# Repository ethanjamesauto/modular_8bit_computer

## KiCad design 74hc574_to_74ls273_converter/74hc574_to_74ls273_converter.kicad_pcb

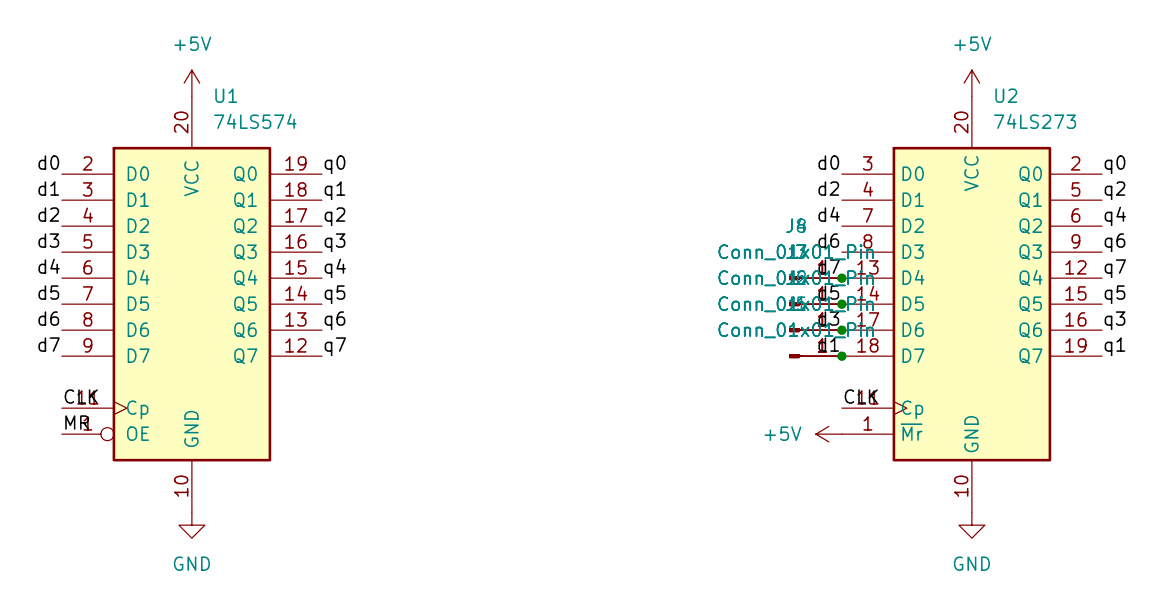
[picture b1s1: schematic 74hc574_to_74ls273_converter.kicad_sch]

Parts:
J1, J2, J3, J4, J5, J6, J7, J8: Conn_01x01_Pin; PinHeader_1x01_P2.54mm_Vertical
U1: 74LS574; DIP-20_W7.62mm
U2: 74LS273; DIP-20_W7.62mm

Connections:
+5V: U1.20 (VCC), U2.1 (~Mr), U2.20 (VCC)
/CLK: U1.11 (Cp), U2.11 (Cp)
/MR: U1.1 (OE)
/d0: U1.2 (D0), U2.3 (D0)
/d1: J1.1, J5.1, U1.3 (D1), U2.18 (D7)
/d2: U1.4 (D2), U2.4 (D1)
/d3: J2.1, J6.1, U1.5 (D3), U2.17 (D6)
/d4: U1.6 (D4), U2.7 (D2)
/d5: J3.1, J7.1, U1.7 (D5), U2.14 (D5)
/d6: U1.8 (D6), U2.8 (D3)
/d7: J4.1, J8.1, U1.9 (D7), U2.13 (D4)
/q0: U1.19 (Q0), U2.2 (Q0)
/q1: U1.18 (Q1), U2.19 (Q7)
/q2: U1.17 (Q2), U2.5 (Q1)
/q3: U1.16 (Q3), U2.16 (Q6)
/q4: U1.15 (Q4), U2.6 (Q2)
/q5: U1.14 (Q5), U2.15 (Q5)
/q6: U1.13 (Q6), U2.9 (Q3)
/q7: U1.12 (Q7), U2.12 (Q4)
GND: U1.10 (GND), U2.10 (GND)

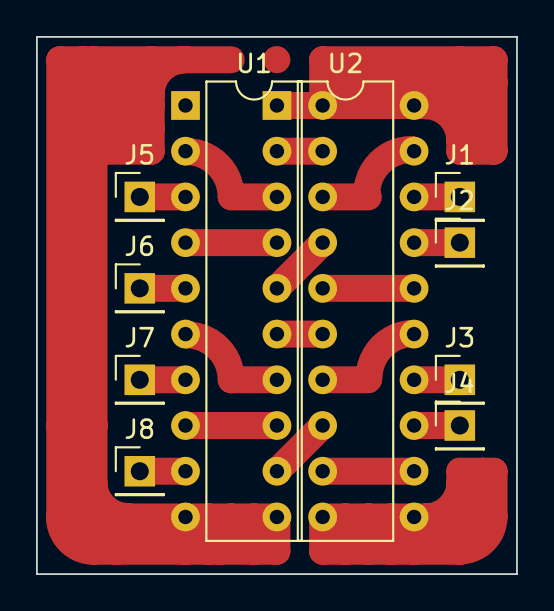
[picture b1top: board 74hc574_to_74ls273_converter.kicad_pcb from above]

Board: 2 copper layers, 26.7 x 29.8 mm, 10 parts (0 on the bottom side), 19 nets.

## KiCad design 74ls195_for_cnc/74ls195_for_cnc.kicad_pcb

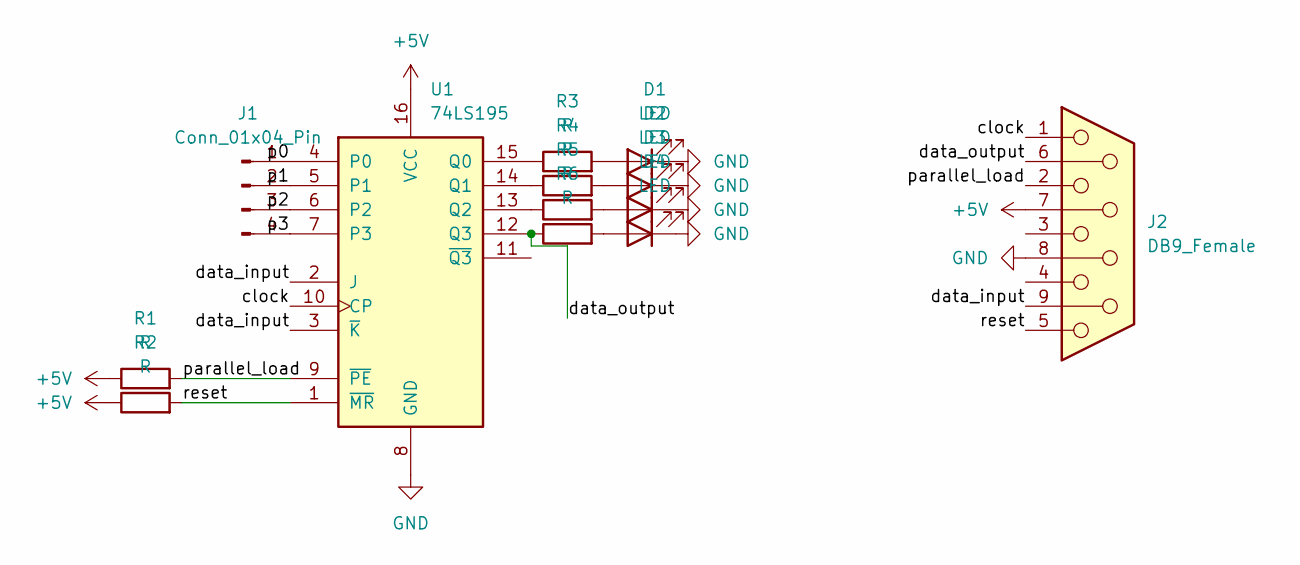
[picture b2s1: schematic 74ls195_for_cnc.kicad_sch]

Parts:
D1, D2, D3, D4: LED; LED_D5.0mm
J1: Conn_01x04_Pin; PinHeader_1x04_P2.54mm_Vertical
J2: DB9_Female; DSUB-9_Female_Horizontal_P2.77x2.54mm_EdgePinOffset9.40mm
R1, R2, R3, R4, R5, R6: R; R_Axial_DIN0204_L3.6mm_D1.6mm_P7.62mm_Horizontal
U1: 74LS195; DIP-16_W7.62mm

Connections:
+5V: J2.7, R1.1, R2.1, U1.16 (VCC)
/clock: J2.1, U1.10 (CP)
/data_input: J2.9, U1.2 (J), U1.3 (~K)
/data_output: J2.6, R6.1, U1.12 (Q3)
/p0: J1.1, U1.4 (P0)
/p1: J1.2, U1.5 (P1)
/p2: J1.3, U1.6 (P2)
/p3: J1.4, U1.7 (P3)
/parallel_load: J2.2, R1.2, U1.9 (~PE)
/reset: J2.5, R2.2, U1.1 (~MR)
GND: D1.1 (K), D2.1 (K), D3.1 (K), D4.1 (K), J2.8, U1.8 (GND)
unnamed: D1.2 (A), R3.2
unnamed: D2.2 (A), R4.2
unnamed: D3.2 (A), R5.2
unnamed: D4.2 (A), R6.2
unnamed: R3.1, U1.15 (Q0)
unnamed: R4.1, U1.14 (Q1)
unnamed: R5.1, U1.13 (Q2)

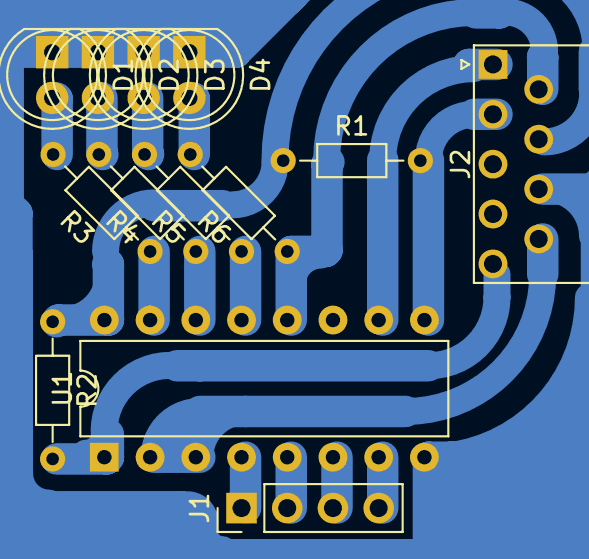
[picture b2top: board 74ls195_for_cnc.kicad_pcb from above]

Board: 2 copper layers, 13 parts (0 on the bottom side), 18 nets.

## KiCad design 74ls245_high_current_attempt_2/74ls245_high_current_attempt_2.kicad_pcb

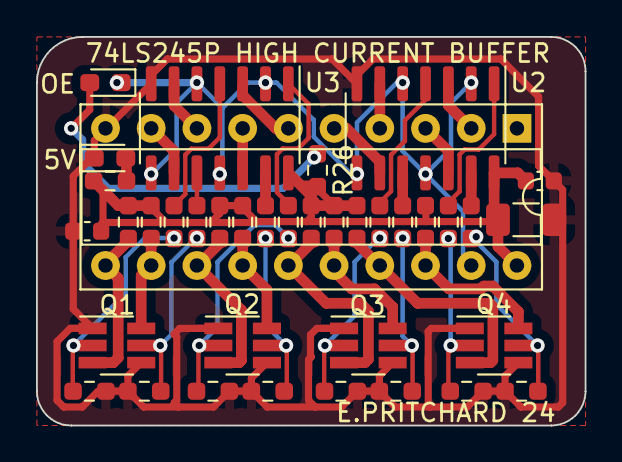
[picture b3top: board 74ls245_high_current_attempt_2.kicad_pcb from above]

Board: 2 copper layers, 30.5 x 21.6 mm, 38 parts (0 on the bottom side), 37 nets.

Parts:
5V: LED; LED_0603_1608Metric_Pad1.05x0.95mm_HandSolder
C1: C; C_1206_3216Metric_Pad1.33x1.80mm_HandSolder
C2, C4: 1uF; C_0603_1608Metric
OE: OE; LED_0603_1608Metric_Pad1.05x0.95mm_HandSolder
Q1, Q2, Q3, Q4: FDG1024NZ; SOT-23-6_Handsoldering
R1, R2, R7, R10, R13, R16, R19, R22: 4.7; R_0603_1608Metric_Pad0.98x0.95mm_HandSolder
R3, R4, R5, R6, R8, R9, R11, R12, R14, R15, R17, R18, R20, R21, R23, R24: 10k; R_0603_1608Metric_Pad0.98x0.95mm_HandSolder
R25, R26: 470; R_0603_1608Metric_Pad0.98x0.95mm_HandSolder
U1: 74LS245_USED_FOR_FOOTPRINT; DIP-20_W7.62mm_Socket
U2, U3: 74LS02; SOIC-14_3.9x8.7mm_P1.27mm

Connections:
+5V: C1.1, C2.1, C4.1, R3.2, R6.2, R9.2, R12.2, R15.2, R18.2, R21.2, R24.2, R25.2, R26.2, U1.20 (VCC), U2.14 (VCC), U3.14 (VCC)
/BUFFER_OE: OE.1 (K), U1.19 (CE), U2.2, U2.5, U2.8, U2.11, U3.2, U3.5, U3.8, U3.11
/in_0: U1.2 (A0), U2.3
/in_1: U1.3 (A1), U2.12
/in_2: U1.4 (A2), U2.6
/in_3: U1.5 (A3), U2.9
/in_4: U1.6 (A4), U3.3
/in_5: U1.7 (A5), U3.12
/in_6: U1.8 (A6), U3.6
/in_7: U1.9 (A7), U3.9
/out_0: Q4.6 (D), R3.1, U1.18 (B0)
/out_1: Q4.3 (D), R6.1, U1.17 (B1)
/out_2: Q3.6 (D), R21.1, U1.16 (B2)
/out_3: Q3.3 (D), R24.1, U1.15 (B3)
/out_4: Q2.6 (D), R15.1, U1.14 (B4)
/out_5: Q2.3 (D), R18.1, U1.13 (B5)
/out_6: Q1.6 (D), R9.1, U1.12 (B6)
/out_7: Q1.3 (D), R12.1, U1.11 (B7)
GND: 5V.1 (K), C1.2, C2.2, C4.2, Q1.1 (S), Q1.4 (S), Q2.1 (S), Q2.4 (S), Q3.1 (S), Q3.4 (S), Q4.1 (S), Q4.4 (S), R4.1, R5.1, R8.1, R11.1, R14.1, R17.1, R20.1, R23.1, U1.10 (GND), U2.7 (GND), U3.7 (GND)
unnamed: 5V.2 (A), R25.1
unnamed: OE.2 (A), R26.1
unnamed: Q1.2 (G), R7.2, R8.2
unnamed: Q1.5 (G), R10.2, R11.2
unnamed: Q2.2 (G), R13.2, R14.2
unnamed: Q2.5 (G), R16.2, R17.2
unnamed: Q3.2 (G), R19.2, R20.2
unnamed: Q3.5 (G), R22.2, R23.2
unnamed: Q4.2 (G), R2.2, R4.2
unnamed: Q4.5 (G), R1.2, R5.2
unnamed: R1.1, U2.13
unnamed: R2.1, U2.1
unnamed: R7.1, U3.4
unnamed: R10.1, U3.10
unnamed: R13.1, U3.1
unnamed: R16.1, U3.13
unnamed: R19.1, U2.4
unnamed: R22.1, U2.10

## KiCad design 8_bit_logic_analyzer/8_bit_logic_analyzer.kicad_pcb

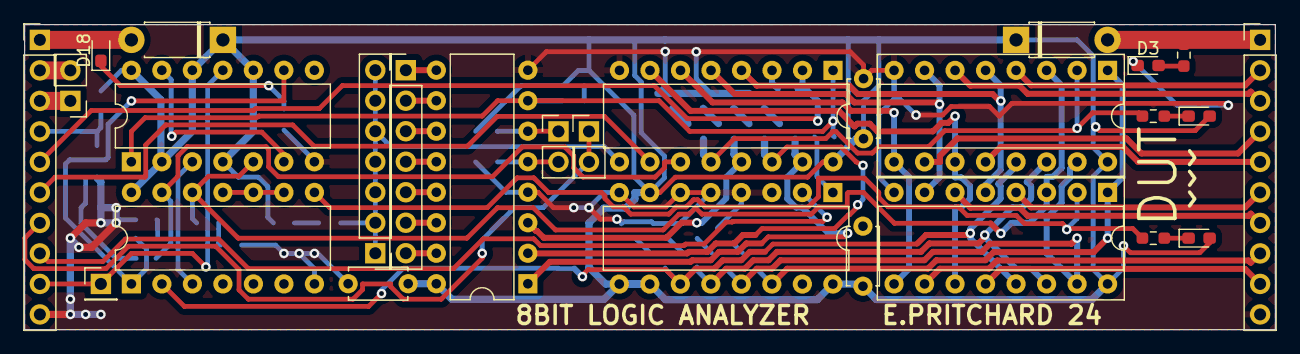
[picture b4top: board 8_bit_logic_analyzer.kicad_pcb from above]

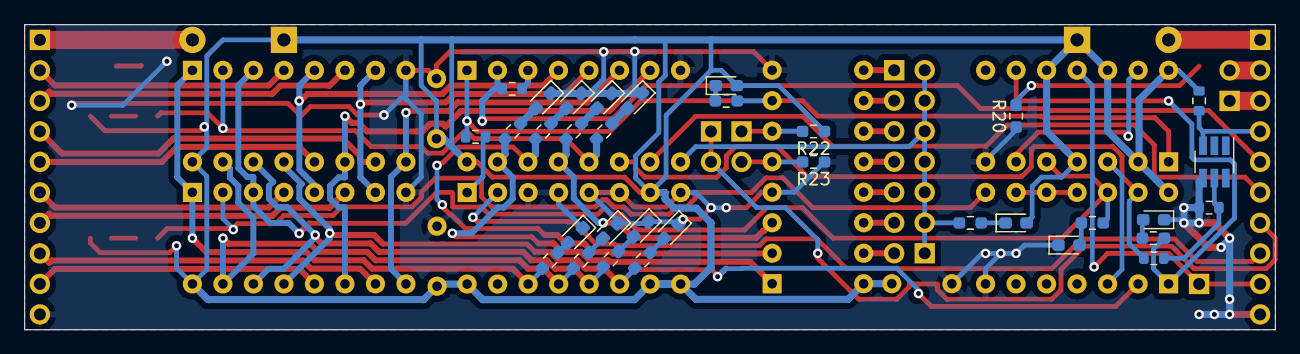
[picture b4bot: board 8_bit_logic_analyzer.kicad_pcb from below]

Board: 2 copper layers, 104.1 x 25.4 mm, 60 parts (33 on the bottom side), 69 nets.

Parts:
C4: 100nF; C_Disc_D4.7mm_W2.5mm_P5.00mm
C10, C11: 1uF; C_Disc_D4.7mm_W2.5mm_P5.00mm
D1, D2: D; D_DO-41_SOD81_P7.62mm_Horizontal
D3, D4, D5, D6, D7, D8, D9, D10, D11, D12, D13, D14, D15, D16, D17, D18: LED; LED_0603_1608Metric_Pad1.05x0.95mm_HandSolder
J1, J2: Conn_01x10_Pin; PinHeader_1x10_P2.54mm_Vertical
J3, J4: Conn_01x07_Pin; PinHeader_1x07_P2.54mm_Vertical
J5, J6, J7: Conn_01x02_Pin; PinHeader_1x02_P2.54mm_Vertical
J8: Conn_01x01_Pin; PinHeader_1x01_P2.54mm_Vertical
Q1: FDG1024NZ; SOT-23-6_Handsoldering
R1: 4.7; R_0603_1608Metric
R2, R3: 10k; R_0603_1608Metric
R4, R6, R7, R8, R9, R10, R11, R12, R13, R14, R15, R16, R17, R18, R19, R20, R22, R23: 470; R_0603_1608Metric_Pad0.98x0.95mm_HandSolder
R5, R21: 0; R_0603_1608Metric
U2, U4: DIP-16_W7.62mm_Socket
U5: 74LS195; DIP-16_W7.62mm
U6: 74LS138; DIP-16_W7.62mm
U7: 74LS74; DIP-14_W7.62mm
U8: 74LS00; DIP-14_W7.62mm
U9: 74LS161; DIP-16_W7.62mm

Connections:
/A: J1.2, U2.4 (D0)
/B: J1.3, U2.6 (D1)
/C: J1.4, U2.10 (D2)
/D: J1.5, U2.12 (D3)
/E: J1.6, U4.4 (D0)
/F: J1.7, U4.6 (D1)
/G: J1.8, U4.10 (D2)
/H: J1.9, U4.12 (D3)
/card_selected: J4.1, J4.2, J4.3, J4.4, J4.5, J4.6, J4.7, R6.2, U5.9 (~PE)
/clear_command: R7.2, R21.2, U5.1 (~MR), U6.7 (O7), U7.1 (~R)
/logic_analyzer_addr_0: R14.2, U2.1 (A0), U4.1 (A0), U9.14 (Q0)
/logic_analyzer_addr_1: R15.2, U2.15 (A1), U4.15 (A1), U9.13 (Q1)
/logic_analyzer_addr_2: R16.2, U2.14 (A2), U4.14 (A2), U9.12 (Q2)
/logic_analyzer_addr_3: R17.2, U2.13 (A3), U4.13 (A3), U8.2, U9.11 (Q3)
/logic_analyzer_data_0: U2.5 (S0_n), U4.5 (S0_n), U5.4 (P0)
/logic_analyzer_data_1: U2.7 (S1_n), U4.7 (S1_n), U5.5 (P1)
/logic_analyzer_data_2: U2.9 (S2_n), U4.9 (S2_n), U5.6 (P2)
/logic_analyzer_data_3: U2.11 (S3_n), U4.11 (S3_n), U5.7 (P3)
/rec_clock: J2.8, U9.2 (CP)
/rec_trig: J2.9, J8.1, U7.11 (C)
/s_clock: J2.6, U5.10 (CP)
/s_cs: J2.7, J6.1, J6.2
/s_data_in: J2.5, R5.1, U5.2 (J)
/s_data_out: J2.4, Q1.3 (D), R3.1
/~ram_0_selected: R11.2, R18.2, U2.2 (~CS), U5.12 (Q3)
/~ram_1_selected: R1.1, U5.11 (~Q3), U8.13
/~record: R13.2, U2.3 (~WE), U4.3 (~WE), U7.5 (Q), U8.12
/~record_halt: U7.6 (~Q), U7.13 (~R)
GND: C4.2, C10.2, C11.2, D3.1 (K), D6.1 (K), D7.1 (K), D8.1 (K), D9.1 (K), D10.1 (K), D11.1 (K), D12.1 (K), D13.1 (K), D14.1 (K), D15.1 (K), J1.10, J2.10, Q1.4 (S), R2.1, R20.1, R23.1, U2.8 (GND), U4.8 (GND), U5.8 (GND), U6.4 (E1), U6.8 (GND), U7.7 (GND), U8.7 (GND), U9.3 (D0), U9.4 (D1), U9.5 (D2), U9.6 (D3), U9.8 (GND)
unnamed: D1.2 (A), D18.2 (A), J2.1
unnamed: D2.2 (A), J1.1, R4.2
unnamed: D3.2 (A), R4.1
unnamed: D4.1 (K), R6.1
unnamed: D5.1 (K), R7.1
unnamed: D6.2 (A), R8.1
unnamed: D7.2 (A), R9.1
unnamed: D8.2 (A), R10.1
unnamed: D9.2 (A), R11.1
unnamed: D10.2 (A), R12.1
unnamed: D11.2 (A), R13.1
unnamed: D12.2 (A), R14.1
unnamed: D13.2 (A), R15.1
unnamed: D14.2 (A), R16.1
unnamed: D15.2 (A), R17.1
unnamed: D16.1 (K), R18.1
unnamed: D17.1 (K), R19.1
unnamed: D18.1 (K), R20.2
unnamed: J2.2, J7.2
unnamed: J2.3, J7.1
unnamed: J3.1, U6.9 (O6)
unnamed: J3.2, U6.10 (O5)
unnamed: J3.3, U6.11 (O4)
unnamed: J3.4, U6.12 (O3)
unnamed: J3.5, U6.13 (O2)
unnamed: J3.6, U6.14 (O1)
unnamed: J3.7, U6.15 (O0)
unnamed: J5.1, R22.2, U6.6 (E3)
unnamed: J5.2, R23.2, U6.5 (E2)
unnamed: Q1.5 (G), R1.2, R2.2
unnamed: R19.2, U4.2 (~CS), U8.8
unnamed: R8.2, U5.15 (Q0), U6.1 (A0)
unnamed: R9.2, U5.14 (Q1), U6.2 (A1)
unnamed: R10.2, U5.13 (Q2), U6.3 (A2)
unnamed: R5.2, U5.3 (~K)
unnamed: U7.3 (C), U8.3
unnamed: R12.2, U7.9 (Q), U8.1
unnamed: U8.9, U8.10, U8.11
unnamed: R21.1, U9.1 (~MR)
VCC: C4.1, C10.1, C11.1, D1.1 (K), D2.1 (K), D4.2 (A), D5.2 (A), D16.2 (A), D17.2 (A), R3.2, R22.1, U2.16 (VCC), U4.16 (VCC), U5.16 (VCC), U6.16 (VCC), U7.2 (D), U7.4 (~S), U7.10 (~S), U7.12 (D), U7.14 (VCC), U8.14 (VCC), U9.7 (CEP), U9.9 (~PE), U9.10 (CET), U9.16 (VCC)

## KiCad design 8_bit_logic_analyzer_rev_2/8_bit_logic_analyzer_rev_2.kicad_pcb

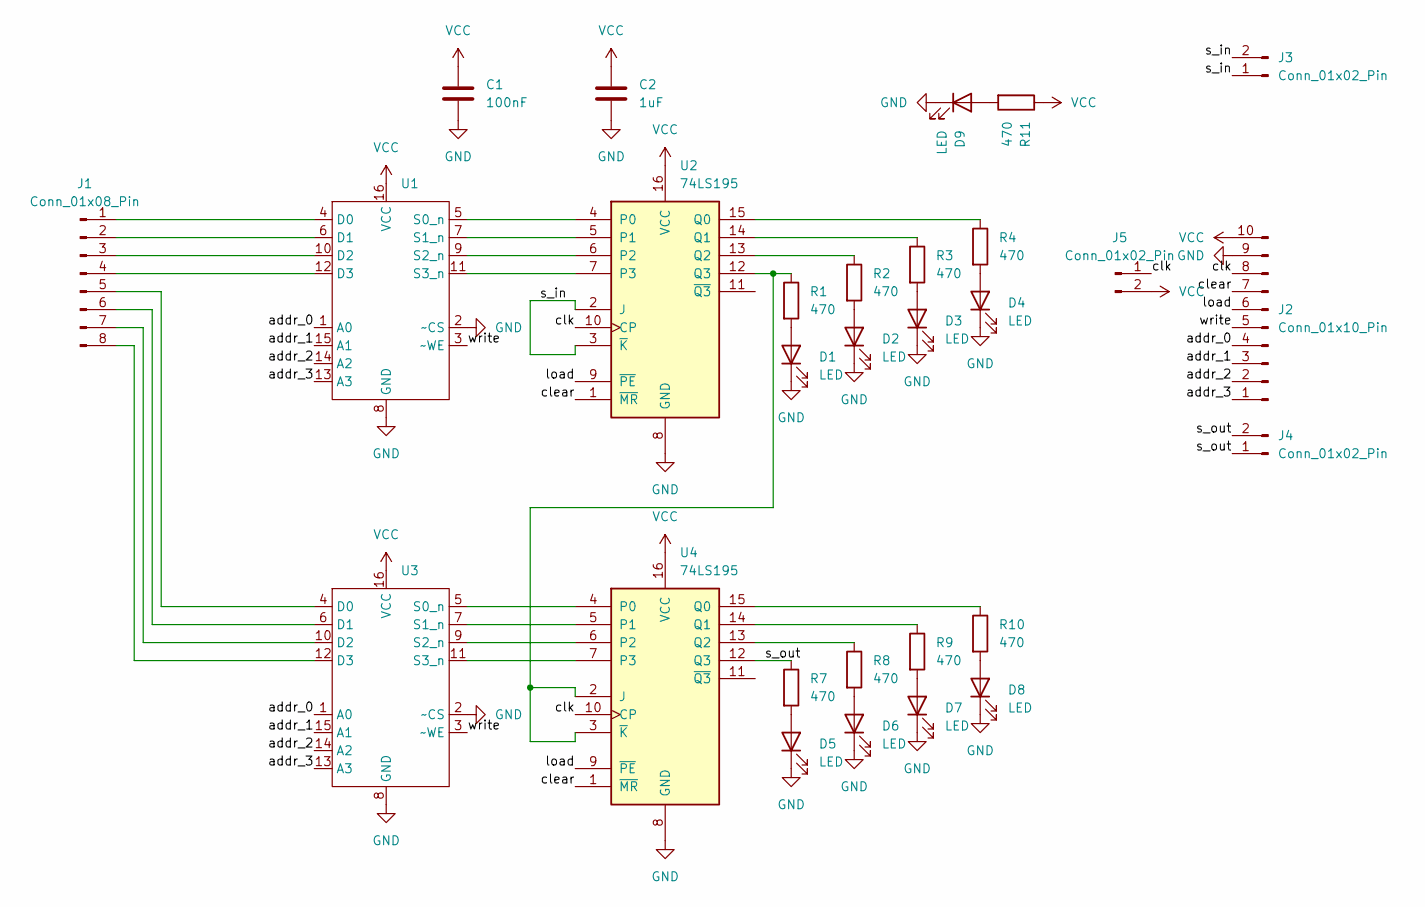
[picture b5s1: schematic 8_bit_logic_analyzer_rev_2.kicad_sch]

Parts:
C1: 100nF; C_Disc_D3.0mm_W2.0mm_P2.50mm
C2: 1uF; C_Disc_D3.0mm_W2.0mm_P2.50mm
D1, D2, D3, D4, D5, D6, D7, D8, D9: LED; R_0603_1608Metric
J1: Conn_01x08_Pin; PinHeader_1x08_P2.54mm_Vertical
J2: Conn_01x10_Pin; PinHeader_1x10_P2.54mm_Vertical
J3, J4, J5: Conn_01x02_Pin; PinHeader_1x02_P2.54mm_Vertical
R1, R2, R3, R4, R7, R8, R9, R10, R11: 470; R_0603_1608Metric
U1, U3: DIP-16_W7.62mm
U2, U4: 74LS195; DIP-16_W7.62mm

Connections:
/addr_0: J2.4, U1.1 (A0), U3.1 (A0)
/addr_1: J2.3, U1.15 (A1), U3.15 (A1)
/addr_2: J2.2, U1.14 (A2), U3.14 (A2)
/addr_3: J2.1, U1.13 (A3), U3.13 (A3)
/clear: J2.7, U2.1 (~MR), U4.1 (~MR)
/clk: J2.8, J5.1, U2.10 (CP), U4.10 (CP)
/load: J2.6, U2.9 (~PE), U4.9 (~PE)
/s_in: J3.1, J3.2, U2.2 (J), U2.3 (~K)
/s_out: J4.1, J4.2, R7.1, U4.12 (Q3)
/write: J2.5, U1.3 (~WE), U3.3 (~WE)
GND: C1.2, C2.2, D1.1 (K), D2.1 (K), D3.1 (K), D4.1 (K), D5.1 (K), D6.1 (K), D7.1 (K), D8.1 (K), D9.1 (K), J2.9, U1.2 (~CS), U1.8 (GND), U2.8 (GND), U3.2 (~CS), U3.8 (GND), U4.8 (GND)
unnamed: D1.2 (A), R1.2
unnamed: D2.2 (A), R2.2
unnamed: D3.2 (A), R3.2
unnamed: D4.2 (A), R4.2
unnamed: D5.2 (A), R7.2
unnamed: D6.2 (A), R8.2
unnamed: D7.2 (A), R9.2
unnamed: D8.2 (A), R10.2
unnamed: D9.2 (A), R11.2
unnamed: J1.1, U1.4 (D0)
unnamed: J1.2, U1.6 (D1)
unnamed: J1.3, U1.10 (D2)
unnamed: J1.4, U1.12 (D3)
unnamed: J1.5, U3.4 (D0)
unnamed: J1.6, U3.6 (D1)
unnamed: J1.7, U3.10 (D2)
unnamed: J1.8, U3.12 (D3)
unnamed: U1.5 (S0_n), U2.4 (P0)
unnamed: U1.7 (S1_n), U2.5 (P1)
unnamed: U1.9 (S2_n), U2.6 (P2)
unnamed: U1.11 (S3_n), U2.7 (P3)
unnamed: R4.1, U2.15 (Q0)
unnamed: R3.1, U2.14 (Q1)
unnamed: R2.1, U2.13 (Q2)
unnamed: R1.1, U2.12 (Q3), U4.2 (J), U4.3 (~K)
unnamed: U3.5 (S0_n), U4.4 (P0)
unnamed: U3.7 (S1_n), U4.5 (P1)
unnamed: U3.9 (S2_n), U4.6 (P2)
unnamed: U3.11 (S3_n), U4.7 (P3)
unnamed: R10.1, U4.15 (Q0)
unnamed: R9.1, U4.14 (Q1)
unnamed: R8.1, U4.13 (Q2)
VCC: C1.1, C2.1, J2.10, J5.2, R11.1, U1.16 (VCC), U2.16 (VCC), U3.16 (VCC), U4.16 (VCC)

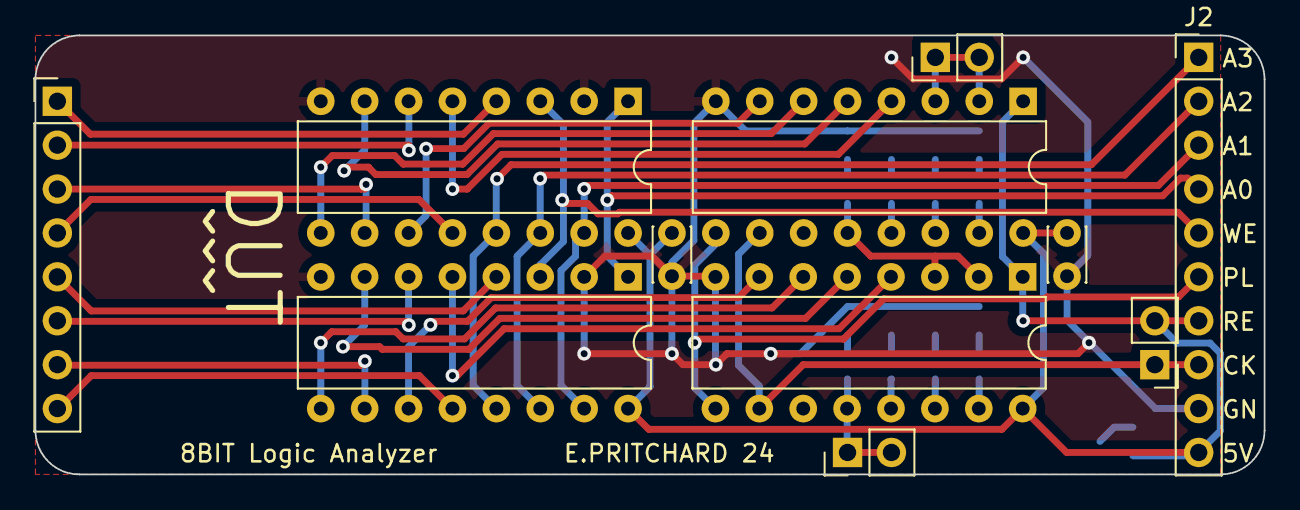
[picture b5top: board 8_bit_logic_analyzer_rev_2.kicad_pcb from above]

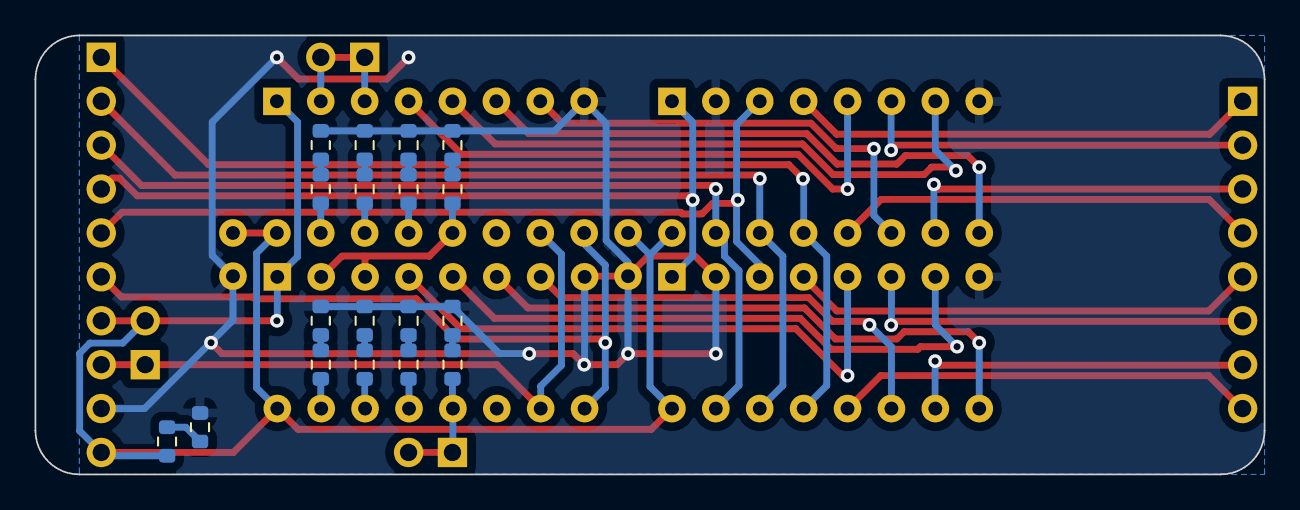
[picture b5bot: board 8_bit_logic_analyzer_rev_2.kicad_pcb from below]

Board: 2 copper layers, 71.1 x 25.4 mm, 29 parts (18 on the bottom side), 44 nets.

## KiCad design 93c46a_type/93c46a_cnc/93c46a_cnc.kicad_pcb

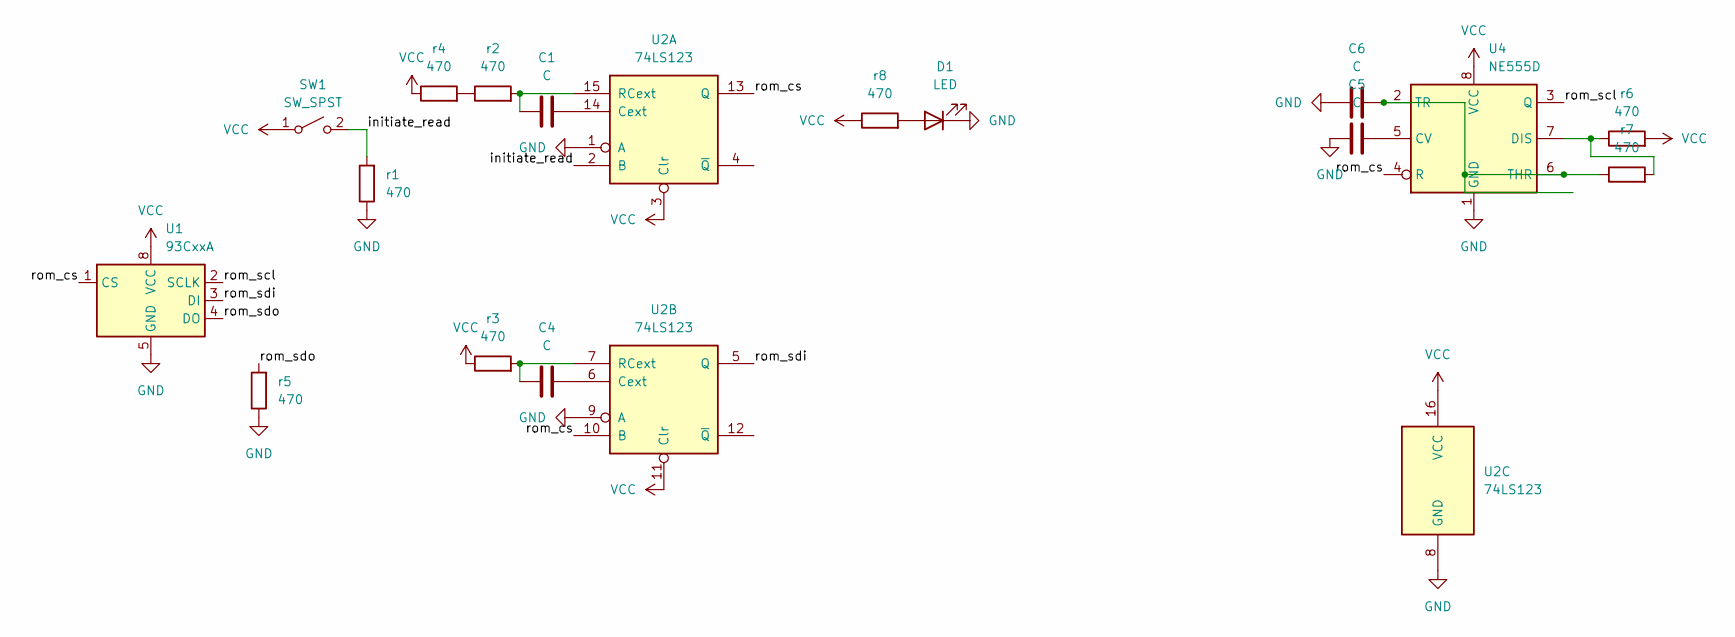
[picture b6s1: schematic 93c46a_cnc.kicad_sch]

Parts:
C1, C4, C5, C6: C; C_Disc_D3.0mm_W2.0mm_P2.50mm
D1: LED; LED_D1.8mm_W3.3mm_H2.4mm
SW1: SW_SPST; C_Disc_D5.1mm_W3.2mm_P5.00mm
U1: 93CxxA; DIP-8_W7.62mm
U2: 74LS123; DIP-16_W7.62mm
U4: NE555D; DIP-8_W7.62mm
r1, r2, r3, r4, r5, r6, r7, r8: 470; R_Axial_DIN0204_L3.6mm_D1.6mm_P5.08mm_Horizontal

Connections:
/initiate_read: SW1.2 (B), U2.2 (B), r1.2
/rom_cs: U1.1 (CS), U2.10 (B), U2.13 (Q), U4.4 (R)
/rom_scl: U1.2 (SCLK), U4.3 (Q)
/rom_sdi: U1.3 (DI), U2.5 (Q)
/rom_sdo: U1.4 (DO), r5.2
GND: C5.2, C6.2, D1.1 (K), U1.5 (GND), U2.1 (A), U2.8 (GND), U2.9 (A), U4.1 (GND), r1.1, r5.1
unnamed: D1.2 (A), r8.2
unnamed: C1.2, U2.14 (Cext)
unnamed: C1.1, U2.15 (RCext), r2.2
unnamed: C4.2, U2.6 (Cext)
unnamed: C4.1, U2.7 (RCext), r3.2
unnamed: C5.1, U4.5 (CV)
unnamed: U4.7 (DIS), r6.1, r7.2
unnamed: C6.1, U4.2 (TR), U4.6 (THR), r7.1
unnamed: r2.1, r4.2
VCC: SW1.1 (A), U1.8 (VCC), U2.3 (Clr), U2.11 (Clr), U2.16 (VCC), U4.8 (VCC), r3.1, r4.1, r6.2, r8.1

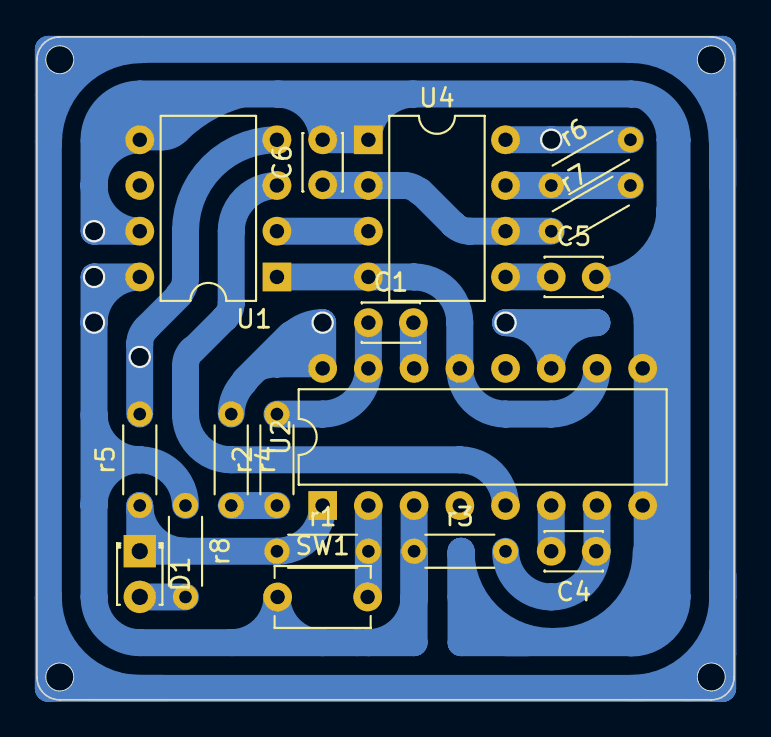
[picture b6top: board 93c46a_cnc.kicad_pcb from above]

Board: 2 copper layers, 38.7 x 36.8 mm, 17 parts (0 on the bottom side), 16 nets.
